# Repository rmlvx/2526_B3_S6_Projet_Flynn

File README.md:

# 🤖 Projet_Flynn

<div align="left">

  <p>

    <br>
    </p>

  <p>
    <em>Un robot autonome suiveur de ligne avec vision par ordinateur, alliant conception électronique et traitement du signal sur Raspberry Pi.</em>
  </p>

</div>

---

## 📖 À propos

Le **Projet Flynn** a pour objectif de concevoir, prototyper et déployer un robot mobile autonome. Sa mission principale est de suivre des trajectoires (lignes noires ou blanches) sur différents types de surfaces grâce à un système de vision par ordinateur embarqué.

Ce projet s'inscrit dans une démarche d'ingénierie complète, combinant :
* **Conception PCB** sous Kicad.
* **Traitement d'image** et du signal pour la navigation.
* **Pilotage moteur** précis via des drivers silencieux.

<!-- ## 🎥 Démonstration

 -->

## 🛠️ Architecture Matérielle (BOM)

Le cerveau du robot est une **Raspberry Pi Zero 2W** qui centralise les données des capteurs et assure le pilotage des actionneurs en temps réel.

| Composant | Qté | Fonction | Réf / Doc |
| :--- | :---: | :---: | :---: |
| **Raspberry Pi Zero 2W** | 1 | Unité centrale de contrôle & Vision | [Datasheet](https://www.raspberrypi.com/documentation/computers/raspberry-pi.html#raspberry-pi-zero-2-w) |
| **LSM6DSOX** | 1 | IMU (Accéléromètre/Gyro) - Mesure X,Y,Z | [Datasheet](https://www.st.com/resource/en/datasheet/lsm6dsox.pdf) |
| **TMC2225** | 2 | Driver Moteur (Contrôle précis et silencieux) | [Datasheet](https://www.analog.com/media/en/technical-documentation/data-sheets/TMC2225_datasheet_rev1.14.pdf) |
| **MCP3208** | 1 | ADC 12-bit - Conversion détection couleur | [Datasheet](https://ww1.microchip.com/downloads/en/DeviceDoc/21298E.pdf) |

## 💻 Stack Technique

* **Langage** : 
* **Conception PCB** : 
* **VCS** : 

## 🚀 Installation et Démarrage

### Prérequis

* Une Raspberry Pi Zero 2W avec **Raspberry Pi OS** configuré.
* Accès SSH ou terminal activé.
* Interfaces **SPI** et **I2C** activées via `raspi-config`.

### Installation

Clonez le dépôt sur votre Raspberry Pi et installez les dépendances nécessaires :

```bash
# Cloner le dépôt
git clone [https://github.com/votre-user/projet-flynn.git](https://github.com/votre-user/projet-flynn.git)

# Accéder au dossier
cd projet-flynn

# Installer les dépendances Python
pip install -r requirements.txt
```

## 👥 L'Équipe

<div align="center">

| Raphaël MILVAUX | Emire GUIOSE | Merihene REKIK | Zoléni KOKOLO ZASSI |
| :---: | :---: | :---: | :---: |
|  |  |  |  |

</div>

<br>

<div align="left">
  <strong>©️ 2026 - Raphaël MILVAUX, Emire GUIOSE, Merihene REKIK, Zoléni KOKOLO ZASSI.</strong><br>
  <em>Projet réalisé dans le cadre de la formation ENSEA.</em>
  <br><br>
  
</div>

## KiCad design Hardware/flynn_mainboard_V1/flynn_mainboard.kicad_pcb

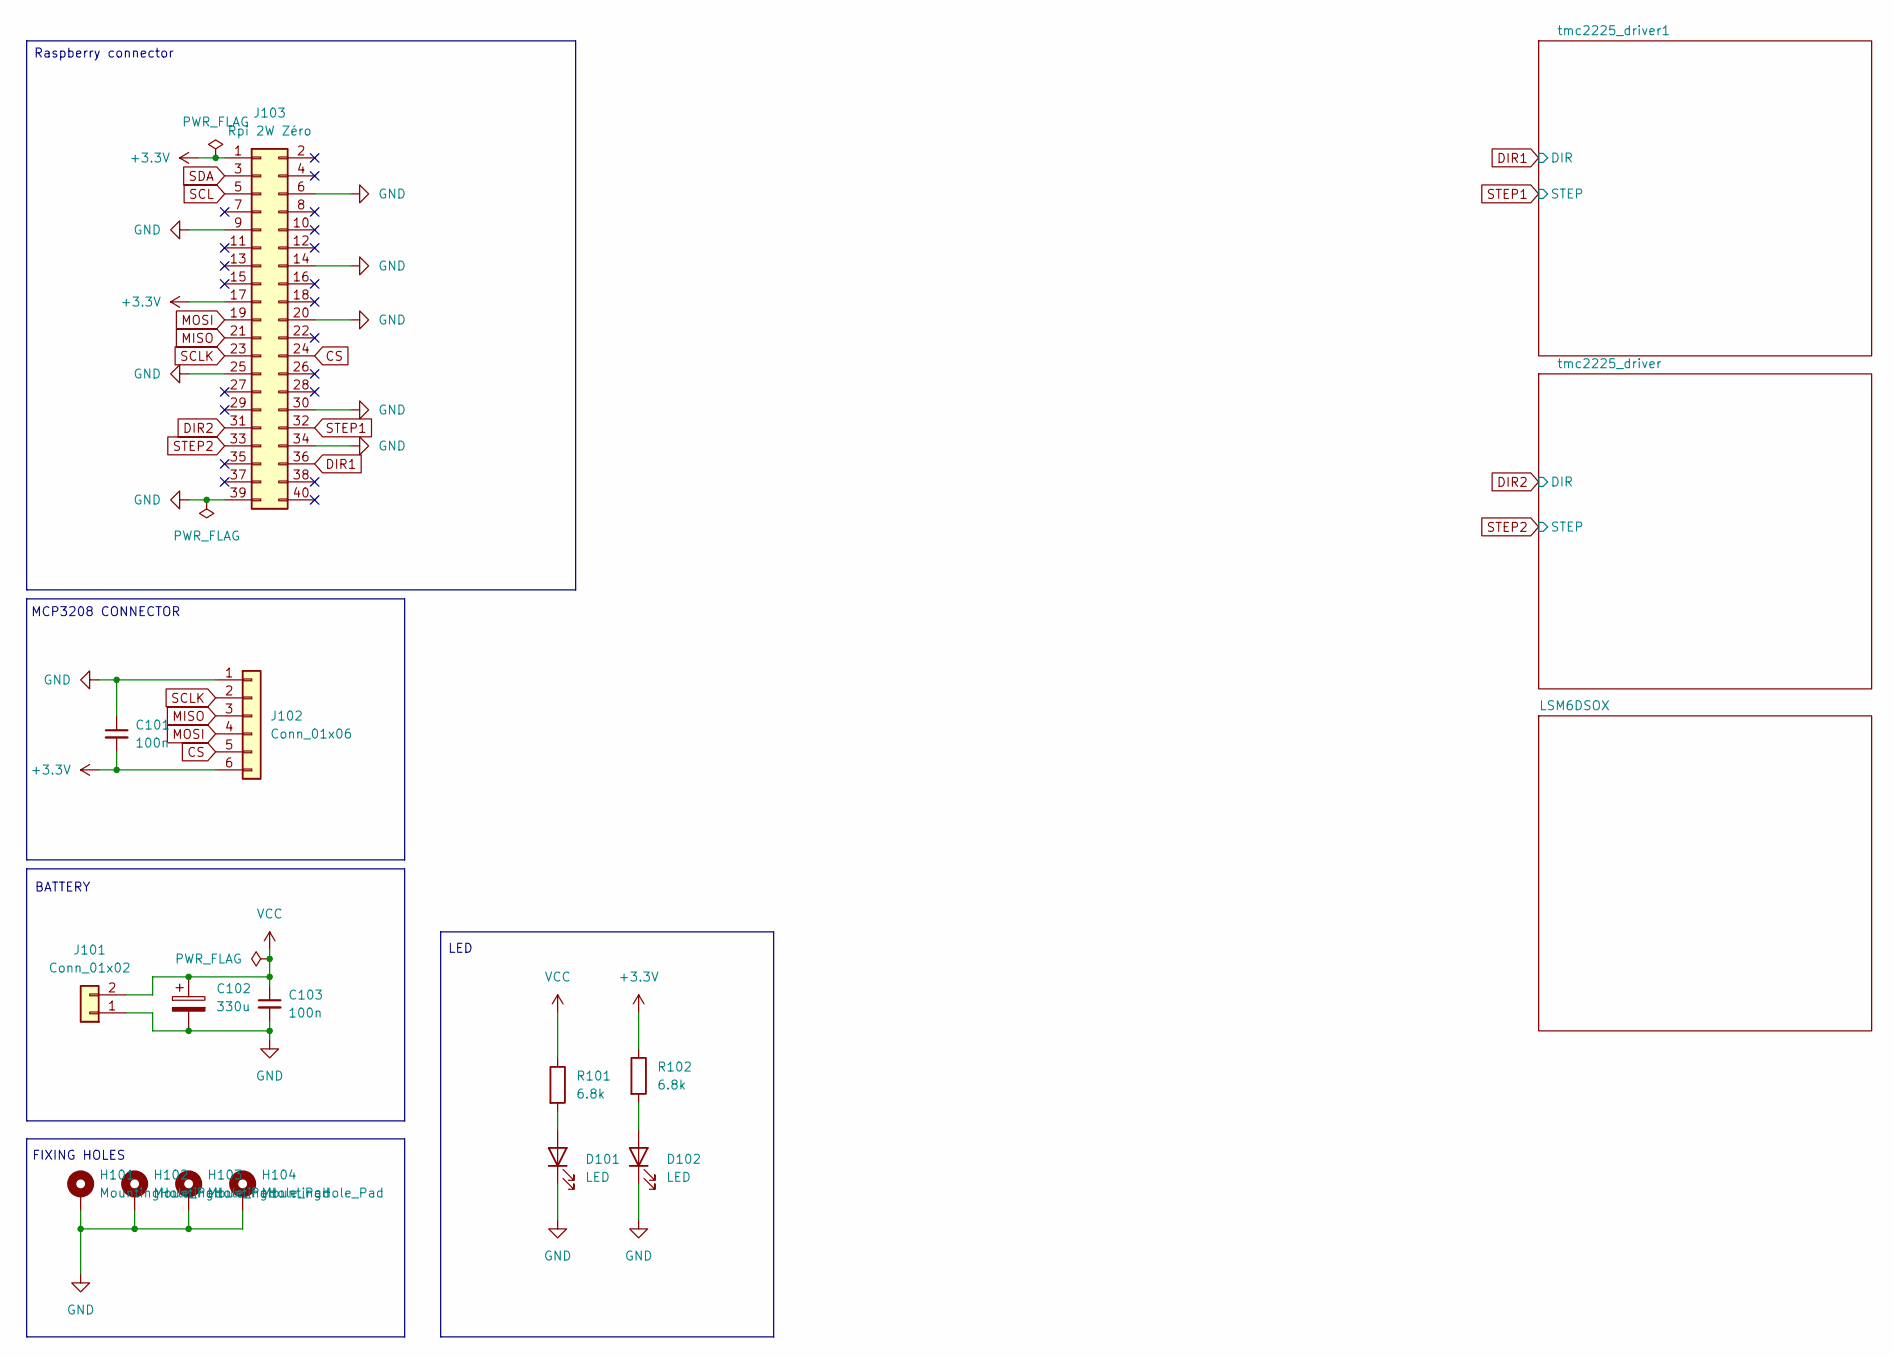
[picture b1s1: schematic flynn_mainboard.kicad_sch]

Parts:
C101, C103: 100n; C_0603_1608Metric
C102: 330u; CP_Elec_6.3x5.4
D101, D102: LED; LED_0603_1608Metric
H101, H102, H103, H104: MountingHole_Pad; MountingHole_2.7mm_M2.5_Pad
J101: Conn_01x02; JST_EH_B2B-EH-A_1x02_P2.50mm_Vertical
J102: Conn_01x06; JST_PH_B6B-PH-K_1x06_P2.00mm_Vertical
J103: Rpi 2W Zéro; PinSocket_2x20_P2.54mm_Vertical
R101, R102: 6.8k; R_0603_1608Metric

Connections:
+3.3V: C101.2, J102.6, J103.1, J103.17, R102.1; also elsewhere on the board
CS: J102.5, J103.24
DIR1: J103.36; also elsewhere on the board
DIR2: J103.31; also elsewhere on the board
GND: C101.1, C102.2, C103.2, D101.1 (K), D102.1 (K), H101.1, H102.1, H103.1, H104.1, J101.1, J102.1, J103.6, J103.9, J103.14, J103.20, J103.25, J103.30, J103.34, J103.39; also elsewhere on the board
MISO: J102.3, J103.21
MOSI: J102.4, J103.19
unnamed: D101.2 (A), R101.2
unnamed: D102.2 (A), R102.2
SCL: J103.5; also elsewhere on the board
SCLK: J102.2, J103.23
SDA: J103.3; also elsewhere on the board
STEP1: J103.32; also elsewhere on the board
STEP2: J103.33; also elsewhere on the board
VCC: C102.1, C103.1, J101.2, R101.1; also elsewhere on the board

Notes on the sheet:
FIXING HOLES
BATTERY
MCP3208 CONNECTOR
LED
Raspberry connector

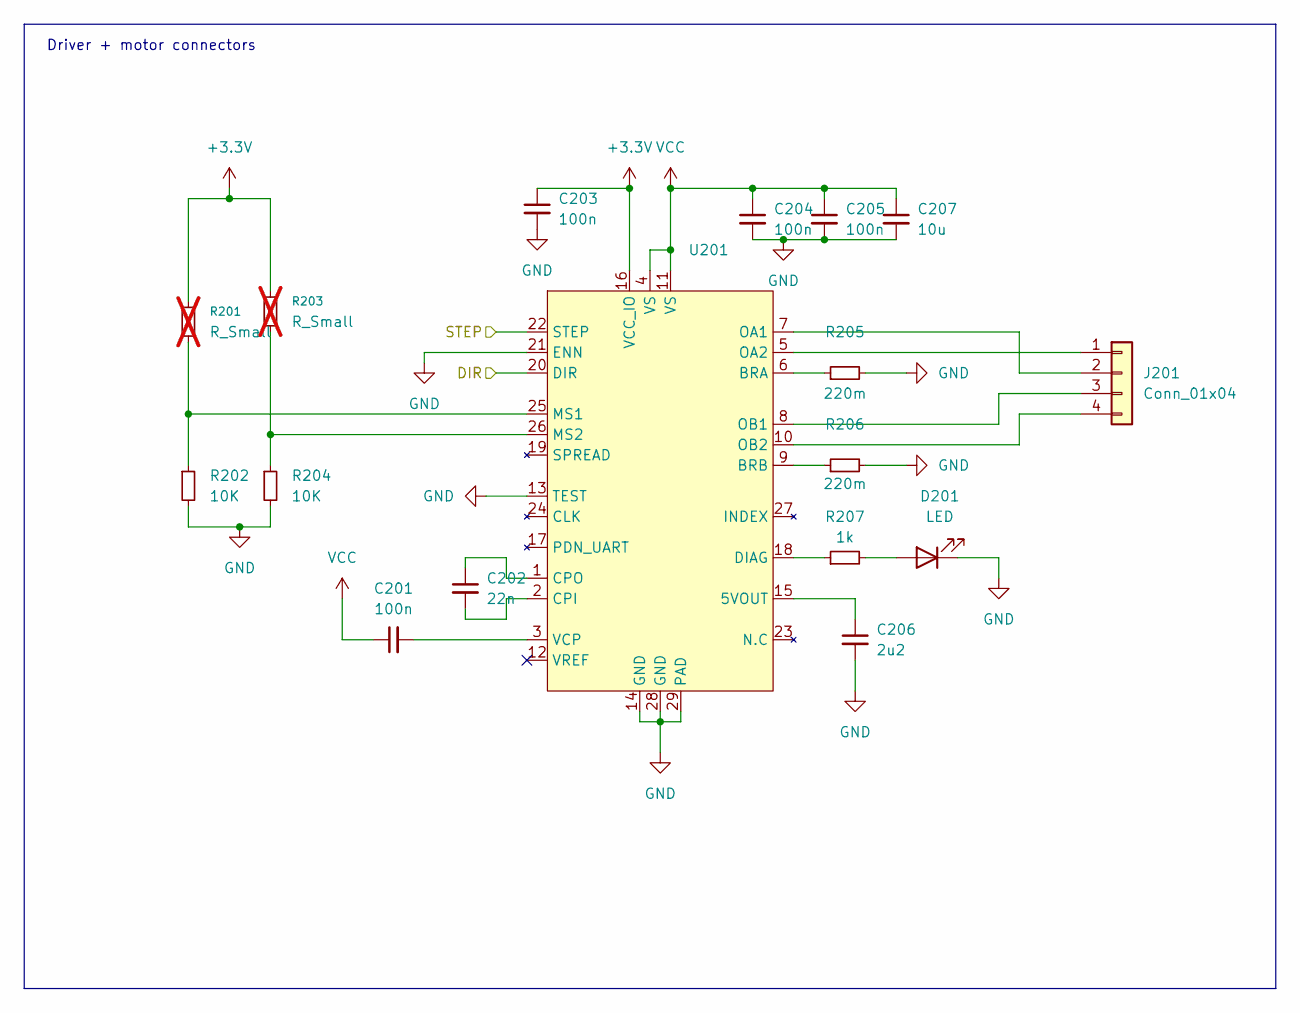
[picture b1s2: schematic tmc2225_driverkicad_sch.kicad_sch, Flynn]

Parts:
C201, C203, C204, C205: 100n; C_0603_1608Metric; MPN 885012206071
C202: 22n; C_0603_1608Metric; MPN 885012206067
C206: 2u2; C_0603_1608Metric; MPN 885 012 106 018
C207: 10u; C_0805_2012Metric; MPN 885012107014
D201: LED; LED_0603_1608Metric
J201: Conn_01x04; JST_PH_B4B-PH-K_1x04_P2.00mm_Vertical
R201, R203: R_Small; R_0603_1608Metric; not fitted
R202, R204: 10K; R_0603_1608Metric
R205, R206: 220m; R_1206_3216Metric
R207: 1k; R_0603_1608Metric
U201: HTSSOP-28-1EP_4.4x9.7mm_P0.65mm_EP2.85x5.4mm_ThermalVias

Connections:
+3.3V: C203.1, R201.1, R203.1, U201.16 (VCC_IO); also elsewhere on the board
DIR2: U201.20 (DIR); also elsewhere on the board
GND: C203.2, C204.2, C205.2, C206.2, C207.2, D201.1 (K), R202.2, R204.2, R205.2, R206.2, U201.13 (TEST), U201.14 (GND), U201.21 (ENN), U201.28 (GND), U201.29 (PAD); also elsewhere on the board
unnamed: D201.2 (A), R207.2
unnamed: J201.1, U201.5 (OA2)
unnamed: J201.2, U201.7 (OA1)
unnamed: J201.3, U201.8 (OB1)
unnamed: J201.4, U201.10 (OB2)
unnamed: C206.1, U201.15 (5VOUT)
unnamed: R205.1, U201.6 (BRA)
unnamed: R206.1, U201.9 (BRB)
unnamed: C202.2, U201.2 (CPI)
unnamed: C202.1, U201.1 (CPO)
unnamed: R207.1, U201.18 (DIAG)
unnamed: R201.2, R202.1, U201.25 (MS1)
unnamed: R203.2, R204.1, U201.26 (MS2)
unnamed: C201.2, U201.3 (VCP)
STEP2: U201.22 (STEP); also elsewhere on the board
VCC: C201.1, C204.1, C205.1, C207.1, U201.4 (VS), U201.11 (VS); also elsewhere on the board

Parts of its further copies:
C401, C403, C404, C405: 100n; C_0603_1608Metric; MPN 885012206071
C402: 22n; C_0603_1608Metric; MPN 885012206067
C406: 2u2; C_0603_1608Metric; MPN 885 012 106 018
D401: LED; LED_0603_1608Metric
J401: Conn_01x04; JST_PH_B4B-PH-K_1x04_P2.00mm_Vertical
R401, R403: R_Small; R_0603_1608Metric; not fitted
R402, R404: 10K; R_0603_1608Metric
R405, R406: 220m; R_1206_3216Metric
R407: 1k; R_0603_1608Metric
U401: HTSSOP-28-1EP_4.4x9.7mm_P0.65mm_EP2.85x5.4mm_ThermalVias

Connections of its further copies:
+3.3V: C403.1, R401.1, R403.1, U401.16 (VCC_IO); also elsewhere on the board
DIR1: U401.20 (DIR); also elsewhere on the board
GND: C403.2, C404.2, C405.2, C406.2, D401.1 (K), R402.2, R404.2, R405.2, R406.2, U401.13 (TEST), U401.14 (GND), U401.21 (ENN), U401.28 (GND), U401.29 (PAD); also elsewhere on the board
unnamed: D401.2 (A), R407.2
unnamed: J401.1, U401.5 (OA2)
unnamed: J401.2, U401.7 (OA1)
unnamed: J401.3, U401.8 (OB1)
unnamed: J401.4, U401.10 (OB2)
unnamed: C406.1, U401.15 (5VOUT)
unnamed: R405.1, U401.6 (BRA)
unnamed: R406.1, U401.9 (BRB)
unnamed: C402.2, U401.2 (CPI)
unnamed: C402.1, U401.1 (CPO)
unnamed: R407.1, U401.18 (DIAG)
unnamed: R401.2, R402.1, U401.25 (MS1)
unnamed: R403.2, R404.1, U401.26 (MS2)
unnamed: C401.2, U401.3 (VCP)
STEP1: U401.22 (STEP); also elsewhere on the board
VCC: C401.1, C404.1, C405.1, U401.4 (VS), U401.11 (VS); also elsewhere on the board

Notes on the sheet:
Driver + motor connectors

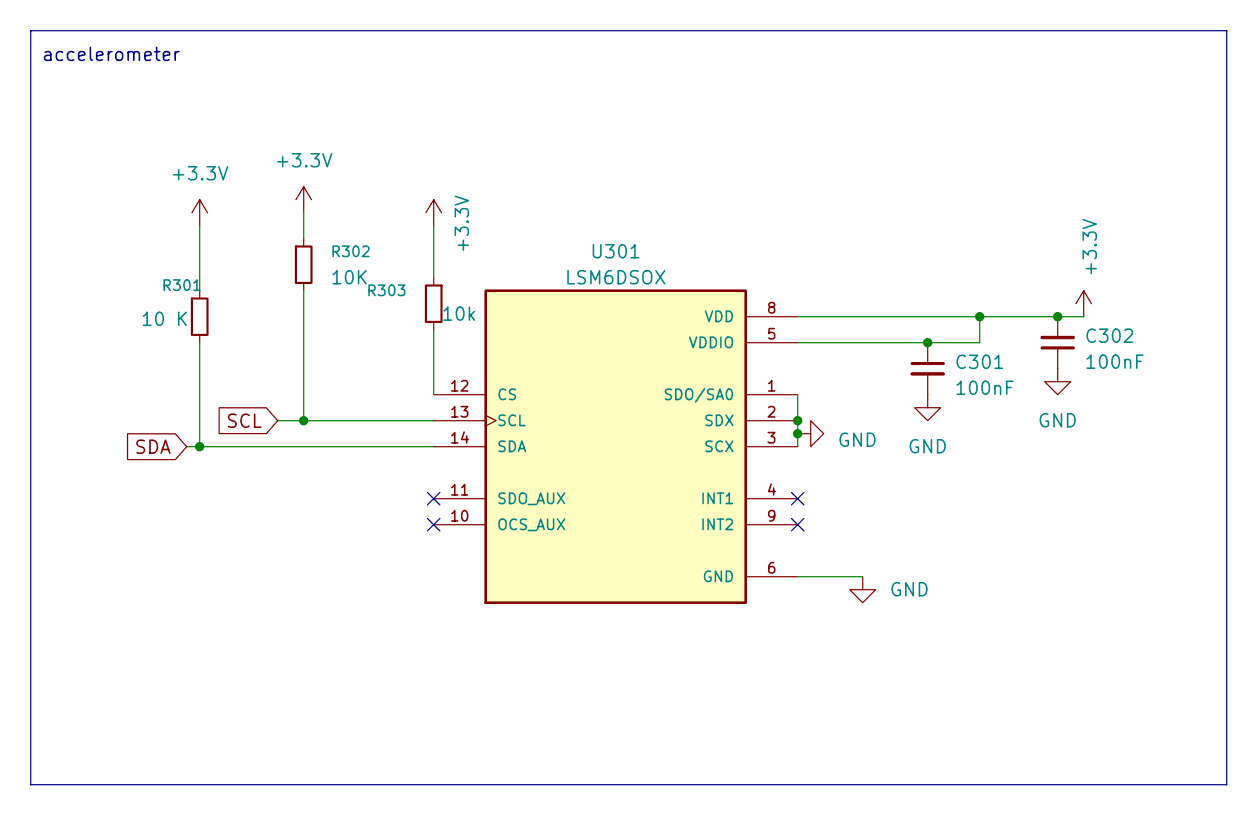
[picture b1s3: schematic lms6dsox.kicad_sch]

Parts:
C301, C302: 100nF; C_0603_1608Metric; MPN 885012206071
R301: 10 K; R_0603_1608Metric
R302: 10K; R_0603_1608Metric
R303: 10k; R_0603_1608Metric
U301: LSM6DSOX; LGA-14_3x2.5mm_P0.5mm_LayoutBorder3x4y; PARTREV 3.0

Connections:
+3.3V: C301.1, C302.2, R301.1, R302.1, R303.1, U301.5 (VDDIO), U301.8 (VDD); also elsewhere on the board
GND: C301.2, C302.1, U301.1 (SDO/SA0), U301.2 (SDX), U301.3 (SCX), U301.6 (GND), U301.7 (GND); also elsewhere on the board
unnamed: R303.2, U301.12 (CS)
SCL: R302.2, U301.13 (SCL); also elsewhere on the board
SDA: R301.2, U301.14 (SDA); also elsewhere on the board

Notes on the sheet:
accelerometer

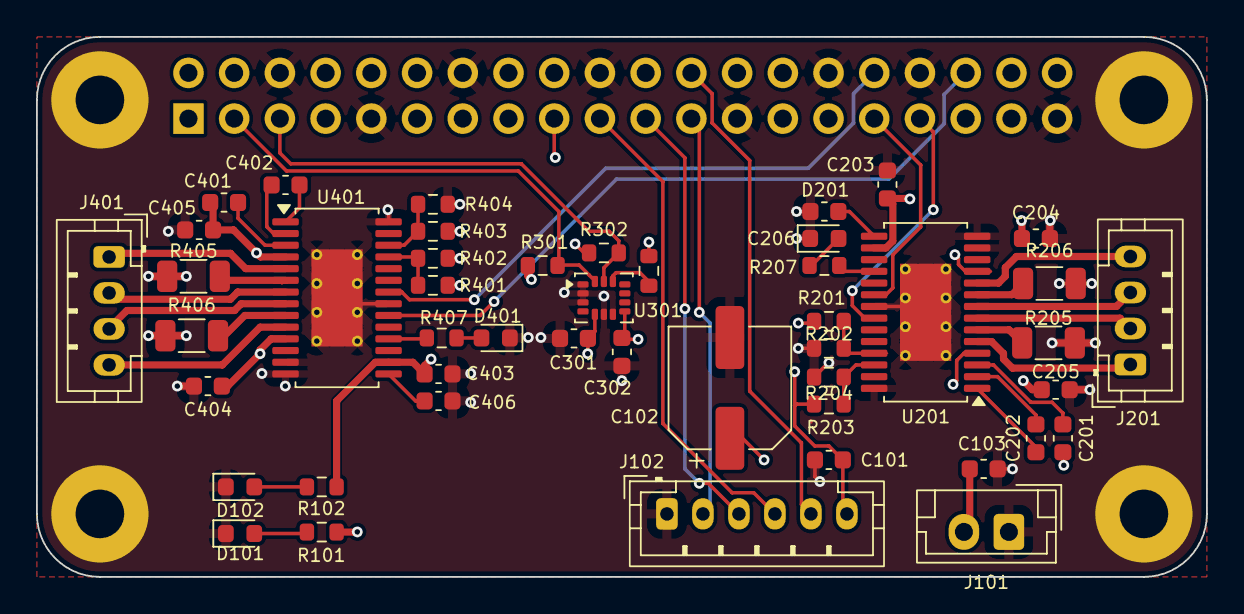
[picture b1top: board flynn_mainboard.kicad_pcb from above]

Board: 4 copper layers, 65.0 x 30.0 mm, 52 parts (1 on the bottom side), 44 nets.

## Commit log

2026-01-20 add folders and kicad files
2026-01-21 Conflit terminé
2026-01-21 Journaling update
2026-01-21 Ajout du schéma
2026-01-21 suppression fichier
2026-01-21 nouvelle version
2026-01-21 Suppression de fichiers temporaires
2026-01-23 Update README & JOURNALING
2026-01-26 version rooté
2026-01-26 Project Update
2026-01-26 Update Journaling
2026-01-26 Projet Flynn complet
2026-01-26 Project_Kicad V1 & V2
2026-01-30 Code added
2026-02-18 Validating Python Code and Journaling Update
2026-02-18 code suitable for PCB
2026-02-19 Journaling Update & Graphic visualization
2026-02-20 Test des moteurs du robot en cours...
2026-02-20 Moteur DROIT OK & Moteur gauche KO
2026-02-20 tests
2026-03-17 Add ADC logic into machine
2026-03-18 Test ADC en cours...
2026-03-20 Aevc 2 capteurs IR défectueux, le moteur roule
2026-03-20 Test des capteurs...
2026-03-20 Les IR qui fonctionnent dirigent bien les moteurs
2026-03-20 Test du PID...
2026-04-14 Kalman added
2026-04-14 Reparation Attempt
2026-04-15 Tentative de réparation du sens de rotation des moteurs
2026-04-16 Test des roues
2026-04-17 Code documentation completed
2026-04-20 Presentation Flynn added in PDF

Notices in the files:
README.md:
License: MIT
